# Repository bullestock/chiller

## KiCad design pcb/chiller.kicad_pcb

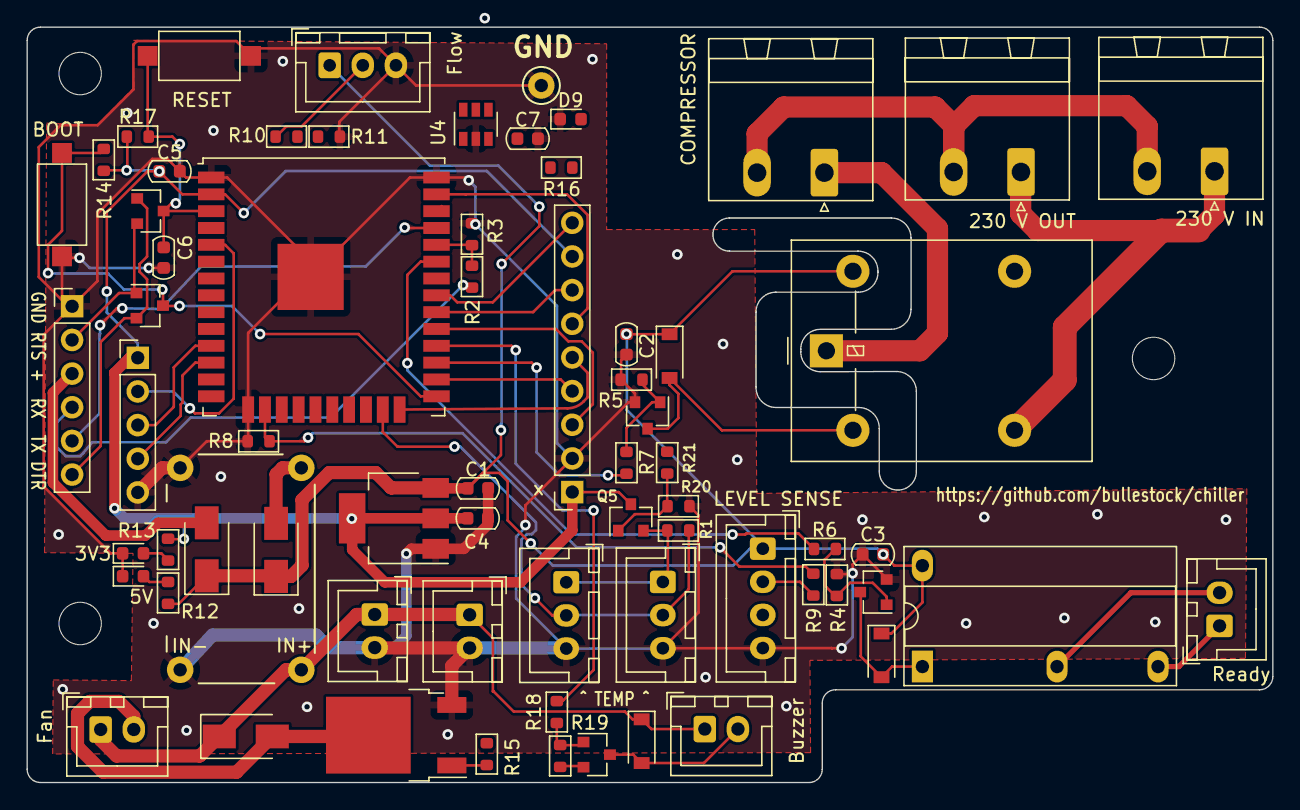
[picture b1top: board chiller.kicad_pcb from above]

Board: 2 copper layers, 94.0 x 57.0 mm, 71 parts (0 on the bottom side), 52 nets.

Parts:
C1, C2, C6: 1u; C_0603_1608Metric
C3, C4: 10u; C_0603_1608Metric
C5, C7: 100n; C_0603_1608Metric
D1, D2, D7: 1N4148; D_SOD-123
D3, D4: MBRA210LT3; D_SMA
D5, D6, D9: LED; LED_0603_1608Metric
D8: SS34; D_SMA
H1, H3, H4: MountingHole; MountingHole_3.2mm_M3
J1: Temp sensor 1; JST_XH_B3B-XH-A_1x03_P2.50mm_Vertical
J2: Temp sensor 2; JST_XH_B3B-XH-A_1x03_P2.50mm_Vertical
J3: Ext; PinHeader_1x05_P2.54mm_Vertical
J4: Mains in; PhoenixContact_MSTBA_2,5_2-G-5,08_1x02_P5.08mm_Horizontal
J5: Mains out; PhoenixContact_MSTBA_2,5_2-G-5,08_1x02_P5.08mm_Horizontal
J6: Compressor; PhoenixContact_MSTBA_2,5_2-G-5,08_1x02_P5.08mm_Horizontal
J7: 12V in; JST_XH_B2B-XH-A_1x02_P2.50mm_Vertical
J8: Pump; JST_XH_B2B-XH-A_1x02_P2.50mm_Vertical
J9: Ready; JST_XH_B2B-XH-A_1x02_P2.50mm_Vertical
J10: Fan; JST_XH_B2B-XH-A_1x02_P2.50mm_Vertical
J11: Display; PinSocket_1x09_P2.54mm_Vertical
J12: Debug; PinHeader_1x06_P2.54mm_Vertical
J13: Conn_01x04; JST_XH_B4B-XH-A_1x04_P2.50mm_Vertical
J14: Flow sensor; JST_XH_B3B-XH-A_1x03_P2.50mm_Vertical
J15: Buzzer; JST_XH_B2B-XH-A_1x02_P2.50mm_Vertical
K1: G5LE-1; Relay_SPDT_Omron-G5LE-1
K2: G6B-1114C-US5DC; DIL-relay
Q1, Q2: MMBT3904; SOT-23
Q3, Q4, Q5, Q7: BSS138; SOT-23
Q6: FDD8447L; TO-252-2
R1: 4k7; R_0603_1608Metric
R2: 1k2; R_0603_1608Metric
R3: 2k2; R_0603_1608Metric
R4: 10K; R_0603_1608Metric
R5, R14, R17, R19, R20: 10k; R_0603_1608Metric
R6: 1K; R_0603_1608Metric
R7, R15, R16, R18, R21: 1k; R_0603_1608Metric
R8, R11: 33k; R_0603_1608Metric
R9, R10: 18k; R_0603_1608Metric
R12: 2k7; R_0603_1608Metric
R13: 1k5; R_0603_1608Metric
SW1, SW2: SW_Push; SW_SPST_CK_RS282G05A3
TP1: TestPoint; TestPoint_Keystone_5000-5004_Miniature
U1: ESP32-WROOM-32; ESP32-WROOM-32U
U2: DSN-MINI-360
U3: AP1117-33; SOT-223-3_TabPin2
U4: 74LVC2G14; SOT-23-6

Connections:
+3V3: C4.1, C5.1, C7.1, J3.1, J11.1, J11.8, Q5.3 (D), R13.1, R14.1, R17.1, U1.2 (VDD), U3.2 (VO), U4.5 (VCC)
+5V: C1.1, C2.1, C3.1, D1.1 (K), D2.1 (K), D3.1 (K), D4.1 (K), J13.1, J14.1, K1.5, K2.2, R12.1, U3.3 (VI)
+12V: D7.1 (K), D8.1 (K), J7.1, J8.1, J10.1, J15.1, U2.IN+
/MCU_RX0: R2.2, R3.1, U1.34 (RXD0/IO3)
/MCU_TX0: J12.5, U1.35 (TXD0/IO1)
/~DTR: J12.6, Q1.2 (E), Q2.1 (B)
/~RTS: J12.2, Q1.1 (B), Q2.2 (E)
Buzzer: R18.1, U1.28 (IO17)
Display_CS: J11.3, U1.29 (IO5)
Display_DC: J11.5, U1.24 (IO2)
Display_Reset: J11.4, U1.26 (IO4)
Display_SCK: J11.7, U1.30 (IO18)
Display_SDI: J11.6, U1.37 (IO23)
Display_SDO: J11.9, U1.31 (IO19)
Ext1: J3.4, U1.12 (IO27)
Ext2: J3.3, U1.11 (IO26)
Ext3: J3.2, U1.5 (SENSOR_VN)
Fan: U1.36 (IO22), U4.1
Flow: R16.1, U1.7 (IO35), U4.4
GND: C1.2, C2.2, C3.2, C4.2, C5.2, C6.2, C7.2, D5.1 (K), D6.1 (K), D9.1 (K), J1.3, J2.3, J3.5, J7.2, J8.2, J11.2, J12.1, J13.4, J14.3, Q3.2 (S), Q4.2 (S), Q6.3 (S), Q7.2 (S), R3.2, R4.2, R5.2, R8.2, R11.2, R19.2, R20.2, SW1.1, SW2.1, TP1.1, U1.1 (GND), U1.15 (GND), U1.38 (GND), U1.39 (GND), U2.IN-, U2.OUT-, U3.1 (GND), U4.2 (GND)
LevelSensor: R8.1, R9.1, U1.16 (IO13)
unnamed: D1.2 (A), K1.2, Q4.3 (D)
unnamed: D2.2 (A), K2.1, Q3.3 (D)
unnamed: D3.2 (A), J12.3
unnamed: D4.2 (A), U2.OUT+
unnamed: D5.2 (A), R12.2
unnamed: D6.2 (A), R13.2
unnamed: D7.2 (A), J15.2, Q7.3 (D)
unnamed: D8.2 (A), J10.2, Q6.2 (D)
unnamed: D9.2 (A), R16.2
unnamed: J1.1, J2.1, Q5.2 (S), R1.1
unnamed: J4.1, J5.1, K1.3
unnamed: J4.2, J5.2, J6.2
unnamed: J6.1, K1.1
unnamed: J9.1, K2.4
unnamed: J9.2, K2.3
unnamed: J12.4, R2.1
unnamed: J13.2, R9.2
unnamed: J14.2, R10.2
unnamed: Q3.1 (G), R4.1, R6.1
unnamed: Q4.1 (G), R5.1, R7.1
unnamed: Q5.1 (G), R20.1, R21.2
unnamed: Q6.1 (G), R15.2
unnamed: Q7.1 (G), R18.2, R19.1
unnamed: R10.1, R11.1, U4.3
unnamed: R15.1, U4.6
OW_PWR: R21.1, U1.10 (IO25)
Relay_comp: R7.2, U1.27 (IO16)
Relay_ready: R6.2, U1.33 (IO21)
TempSensor: J1.2, J2.2, R1.2, U1.23 (IO15)
~BOOT: Q1.3 (C), R14.2, SW1.2, U1.25 (IO0)
~RESET: C6.1, Q2.3 (C), R17.2, SW2.2, U1.3 (EN)

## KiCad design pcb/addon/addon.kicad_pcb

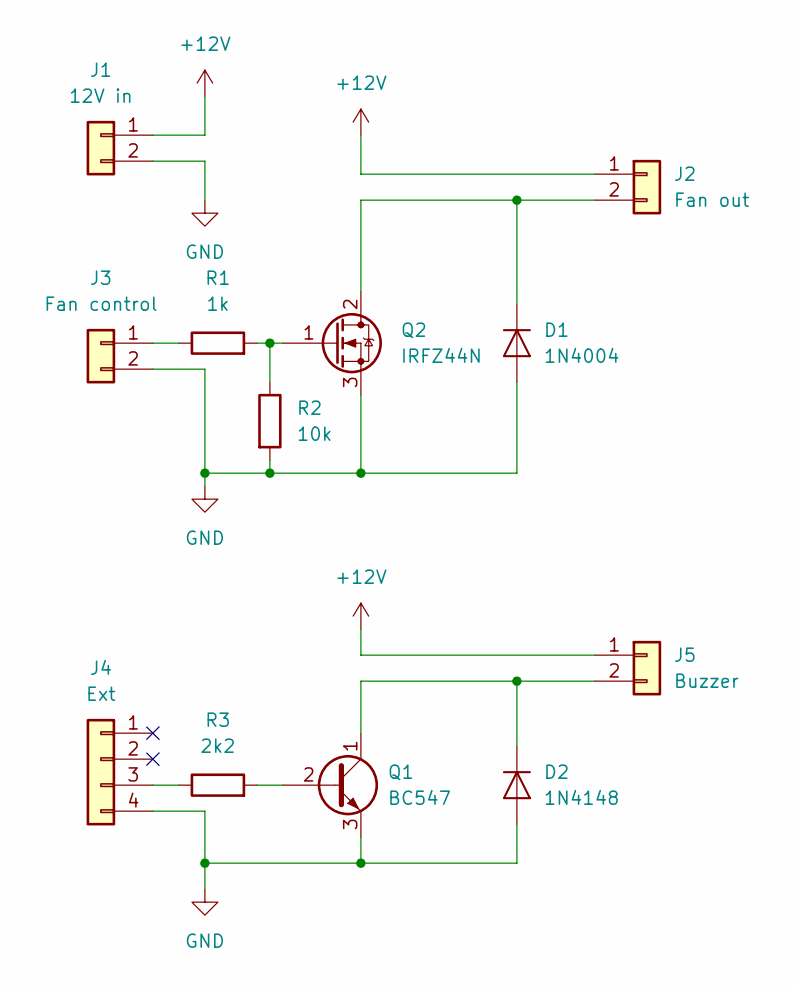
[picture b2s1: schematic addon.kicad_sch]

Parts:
D1: 1N4004; D_DO-41_SOD81_P10.16mm_Horizontal
D2: 1N4148; D_DO-35_SOD27_P7.62mm_Horizontal
J1: 12V in; JST_XH_B2B-XH-A_1x02_P2.50mm_Vertical
J2: Fan out; JST_XH_B2B-XH-A_1x02_P2.50mm_Vertical
J3: Fan control; JST_XH_B2B-XH-A_1x02_P2.50mm_Vertical
J4: Ext; JST_XH_B4B-XH-A_1x04_P2.50mm_Vertical
J5: Buzzer; JST_XH_B2B-XH-A_1x02_P2.50mm_Vertical
Q1: BC547; TO-92L_Inline_Wide
Q2: IRFZ44N; TO-220-3_Vertical
R1: 1k; R_Axial_DIN0204_L3.6mm_D1.6mm_P7.62mm_Horizontal
R2: 10k; R_Axial_DIN0207_L6.3mm_D2.5mm_P10.16mm_Horizontal
R3: 2k2; R_Axial_DIN0207_L6.3mm_D2.5mm_P7.62mm_Horizontal

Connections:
+12V: J1.1, J2.1, J5.1
GND: D1.2 (A), D2.2 (A), J1.2, J3.2, J4.4, Q1.3 (E), Q2.3 (S), R2.2
unnamed: D1.1 (K), J2.2, Q2.2 (D)
unnamed: D2.1 (K), J5.2, Q1.1 (C)
unnamed: J3.1, R1.1
unnamed: J4.3, R3.1
unnamed: Q1.2 (B), R3.2
unnamed: Q2.1 (G), R1.2, R2.1

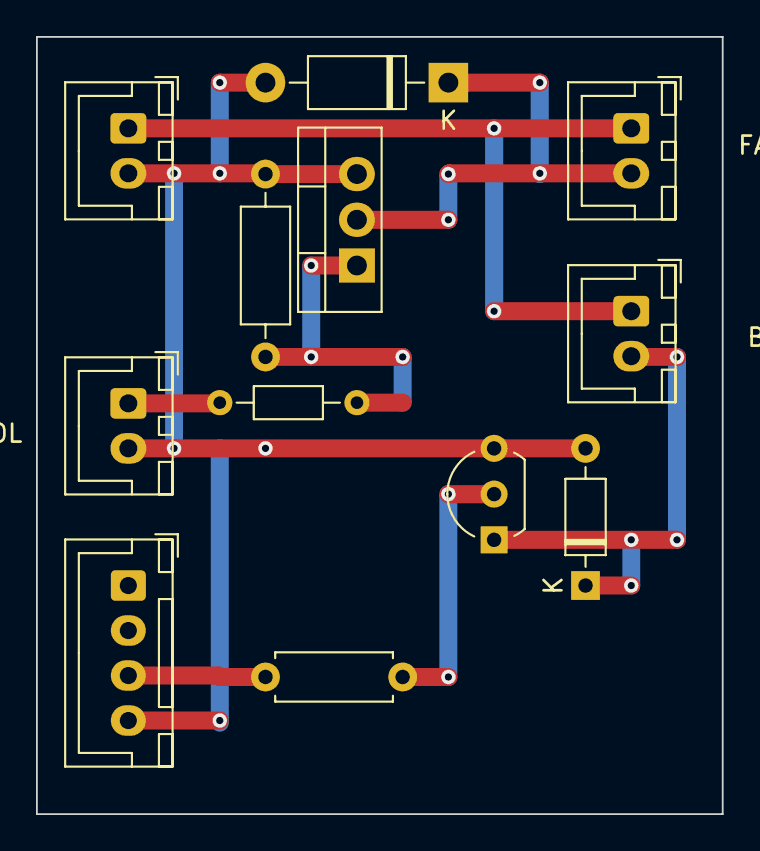
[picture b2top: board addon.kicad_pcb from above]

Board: 2 copper layers, 38.1 x 43.2 mm, 12 parts (0 on the bottom side), 8 nets.

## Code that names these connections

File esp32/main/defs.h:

#pragma once

#include <driver/gpio.h>
#include <esp_adc/adc_oneshot.h>

constexpr const char* VERSION = "0.4.2";

// Pin definitions
constexpr const auto PIN_DISP_DC = (gpio_num_t) 2;
constexpr const auto PIN_DISP_RESET = (gpio_num_t) 4;
constexpr const auto PIN_DISP_CS = (gpio_num_t) 5;
constexpr const auto PIN_DISP_SCK = (gpio_num_t) 18;
constexpr const auto PIN_DISP_SDO = (gpio_num_t) 19;
constexpr const auto PIN_DISP_SDI = (gpio_num_t) 23;
constexpr const auto PIN_BUZZER = (gpio_num_t) 17;
constexpr const auto PIN_EXT_1 = (gpio_num_t) 27;
constexpr const auto PIN_EXT_2 = (gpio_num_t) 26;
constexpr const auto PIN_LEVEL = (gpio_num_t) 13;
constexpr const auto PIN_TEMP = (gpio_num_t) 15;
constexpr const auto PIN_RELAY_COMP = (gpio_num_t) 16;
constexpr const auto PIN_RELAY_RDY = (gpio_num_t) 21;
constexpr const auto PIN_FAN = (gpio_num_t) 22;
constexpr const auto PIN_FLOW = (gpio_num_t) 35;

constexpr const char* TAG = "CHLR";

constexpr const char* HIGHEST_INDEX_IS_WATER_KEY = "HIIW";
constexpr const char* FAN_PWM_KEY = "FPWM";

// High/low temperature for thermostat (degrees)
constexpr const float LOW_TEMP = 20.0;
constexpr const float HIGH_TEMP = 25.0;

// Warn above this temperature
constexpr const float WATER_WARN_TEMP = 30.0;
constexpr const float COMPRESSOR_WARN_TEMP = 60.0;

// Halt operation above this temperature
constexpr const float WATER_HOT_TEMP = 35.0;
constexpr const float COMPRESSOR_HOT_TEMP = 70.0;

// High/low temperature for fan control
constexpr const float COMPRESSOR_FAN_LOW_TEMP = 28.0;
constexpr const float COMPRESSOR_FAN_HIGH_TEMP = 30.0;

// Halt operation if sensor reports less than this temperature
constexpr const float MIN_ACCEPTABLE_TEMP = 10.0;
// Halt operation if sensor reports more than this temperature
constexpr const float MAX_ACCEPTABLE_TEMP = 100.0;

// Minimum flow (l/h)
constexpr const int MIN_FLOW = 50;

// Number of temperature sensor readings to average
constexpr const int TEMP_AVERAGES = 5;

// Number of consecutive errors to trigger fault condition
constexpr const int CONSECUTIVE_ERRORS = 5;

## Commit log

2015-09-01 Initial.
2015-09-08 Show temperature, flow, and status.
2015-09-10 Implement rest of the control logic.
2015-11-10 Add serial debug.
2015-11-10 Do not use a hard coded sensor address.
2016-06-25 Add temperature sensor validation.
2016-06-26 Use moving average of temperature. Show version number on boot.
2016-06-26 Require 5 consecutive errors to signal failure. Add buzzer support.
2016-11-18 Add audio feedback.
2016-11-18 Add schematic for new control board.
2017-03-25 Finish diagram; add Arduino code for display test.
2017-03-25 Add initialization code.
2017-03-25 Add annoying failure sound.
2017-03-31 Fix bugs.
2017-04-01 Add flow sensor simulator.
2017-04-01 Add pullups, serial port connector.
2017-04-01 Rename, add Makefile.
2017-05-11 Add flow measurement.
2017-05-11 Average temperatures.
2017-05-11 Implement logic.
2017-05-12 Add fan control.
2017-05-12 Change temperature captions.
2017-05-12 Fix overflow error.
2017-05-12 Add fan control. Drive SSR from 12V.
2017-05-13 Show firmware version on startup.
2017-06-17 Keep fan on for a while after switching compressor off.
2017-06-17 Pics!
2017-07-06 Tweak temperatures, and provide audible warning if temperature exceeds WARN_TEMP.
2017-07-13 Control fan according to compressor temperature.
2017-07-13 Keep track of compressor temperature.
2018-10-16 Add hysteresis for fan control.
2018-10-16 Prepare for proper PCB.
2018-10-19 Finalize schematic.
2018-10-19 Fix footprints, place all components.
2018-10-20 Complete routing.
2018-10-20 Make pretty.
2018-10-24 Work on schematic.
2018-12-15 Update for WAVGAT.
2018-12-15 Change baud rate, fix version display.
2018-12-15 Reduce startup time by reading temp sensors in parallel.
2018-12-15 Compute flow immediately.
2019-01-20 Fix errors: - Relay wrong footprint - Q2 switched D and G
2019-01-21 Update potentiometer and relay footprints.
2019-01-31 Fix beep on startup.
2021-06-26 Update to KiCad 5 format.
2022-05-24 Clean up.
2023-02-25 Test fit.
2023-02-25 Add mounting holes, enlarge retainers.
2023-02-25 Split into two.
2023-02-26 Add part2 code.
2023-02-26 Enlarge.
2023-02-26 Add.
2023-03-14 Now fits inside tank.
2023-03-15 Clip for holding together the two coil holders.
2023-03-19 First saved version.
2023-03-19 Tweak.
2023-04-06 Add cutout for L-profile.
2023-04-22 Add stuff.
2023-04-22 Printable version.
2023-04-23 Basic shape.
2023-04-23 Finish.
2023-04-23 Retaining clip.
2023-05-30 First shot.
2023-05-30 Complete.
2023-05-31 Adjust height
2023-05-31 Update.
2023-06-02 Add ingress pipe.
2023-06-02 Add straight ingress.
2023-06-03 Double version.
2023-06-04 Add more stuff.
2023-06-04 Start designing new PCB.
2023-06-04 Fix width.
2023-06-04 Add components.
2023-06-04 Add Inkscape files.
2023-06-04 Move display connections, etc.
2023-06-05 Finish routing.
2023-06-05 Apply finishing touches.
2023-06-23 Add hwtest.
2023-06-23 Cleanup.
2023-06-23 Add firmware skeleton.
2023-06-23 Add diodes.
2023-06-23 Fix pin definition.
2023-06-25 Add TFT_eSPI library and hack it to work without Arduino component.
2023-07-01 Add temp sensor support.
2023-07-09 Start implementing main loop.
2023-07-09 Oops.
2023-07-10 Start adding forgotten features.
2023-07-10 Complete main loop implementation.
2023-07-10 Add LEDs.
2023-07-10 Move J9.
2023-07-10 Fix layout.
2023-07-10 Fix rotation.
2023-07-10 Prepare for simulation.
2023-07-12 Version 2 ready for ordering.
2023-07-12 Clean up silk screen
2023-07-12 Rail for connecting 6 60 mm fans.
2023-07-13 Bracket for 10 mm square aluminium tubing.
2023-07-15 First attempt.
2023-07-15 Use loft().
2023-07-16 Enlarge hole.
2023-07-17 Bezel for display.
2023-07-17 Hook for suspending fans.
2023-07-17 Upper part of front.
2023-07-17 Lower part of front.
2023-07-17 Mount for top front plate.
2023-07-17 Left part of bottom.
2023-07-17 Right part of bottom.
2023-07-17 Backet for assembling bottom pieces.
2023-07-18 Fix errors.
2023-07-21 Final adjustments for V2.
2023-07-22 Make reinforcement longer.
2023-07-22 Add flanges for sideplate screws.
2023-07-23 Add hole for insert.
2023-07-23 Undo.
2023-07-23 Adapter.
2023-07-25 Pin for hinge.
2023-07-25 Tune.
2023-07-26 Washer for sides.
2023-08-05 Remove fittings.
2023-08-05 Rename vars.
2023-08-20 Increase distance between pipes.
2023-09-23 Fix pin number for flow sensor.
2023-09-25 Update R10/R11 values
2023-09-25 Add BOOT switch
2023-09-27 Add Display class.
2023-09-28 Fix display bugs. Move buzzer to EXT1.
2023-09-28 Fix error handling.
2023-09-30 Adapt timing for mechanical buzzer.
2023-10-04 Add addon board.
2023-10-06 Add more test commands.
2023-10-07 Add test_buzzer command.
2023-10-07 Add missing file.
2023-10-07 Fix fan pin definition.
2023-10-07 Fix fan logic level.
2023-10-07 Add test_level, test_current commands
2023-10-09 Move fan and buzzer MOSFETs onto main board.
2023-10-09 Route.
2023-10-14 Check level sensor. Add Buzzer class.
2023-10-22 Make ridges into spheres.
2023-10-23 Fix top chamfer.
2023-10-23 Add male-male top moulding.
2023-10-23 Fix chamfers.
2023-10-23 FM version.
2023-10-25 Add slots for handle
2023-10-27 Fix handle holes.
2023-10-27 Add skew.
2023-10-27 Enlarge handle cutouts.
2023-10-29 Remove slot etc.
2023-10-29 Oops, forgot to save.
2023-11-06 Retry detection of DS18B20.
2023-11-06 Finalize.
2023-11-06 Add pullups
2023-11-07 Add support for swapping temp sensors.
2023-11-09 Init HW before display.
2023-11-11 Reduce font size during init
2023-11-11 Reduce debug noise.
2023-11-11 Fix bugs in temperatur averaging.
2023-11-11 Fix display flicker
2023-11-12 Use PWM for fan; reinitialize OWB bus before retrying DS18B20 detection.
2023-11-12 Add missing components.
2023-11-12 Place all components.
2023-11-12 Order
2023-11-13 Move buzzer to its own pin.
2023-11-13 Add fan PWM setting.
2023-12-05 Invert fan PWM signal.
2023-12-05 Make fan test faster.
2023-12-05 Update for IDF 5.1.2.
2023-12-05 Fix footprint.
2023-12-06 Make compressor test less aggressive.
2023-12-06 Fix fan whine.
2024-02-08 Allow a few temp sensor errors before panicking.
2024-05-10 First draft.
2024-05-11 Part 2
2024-05-11 Add seal, lid outline.
2024-05-12 Add cable cutouts.
2024-05-12 Adjust edge dimensions. Rework lid.
2024-05-16 Central part.
2024-05-19 Add 3 corners.
2024-05-19 Add inverters, stitching vias.
2024-05-19 Fix ERC issues.
2024-05-19 Add new components.
2024-05-20 Add MOSFET to control OneWire power.
